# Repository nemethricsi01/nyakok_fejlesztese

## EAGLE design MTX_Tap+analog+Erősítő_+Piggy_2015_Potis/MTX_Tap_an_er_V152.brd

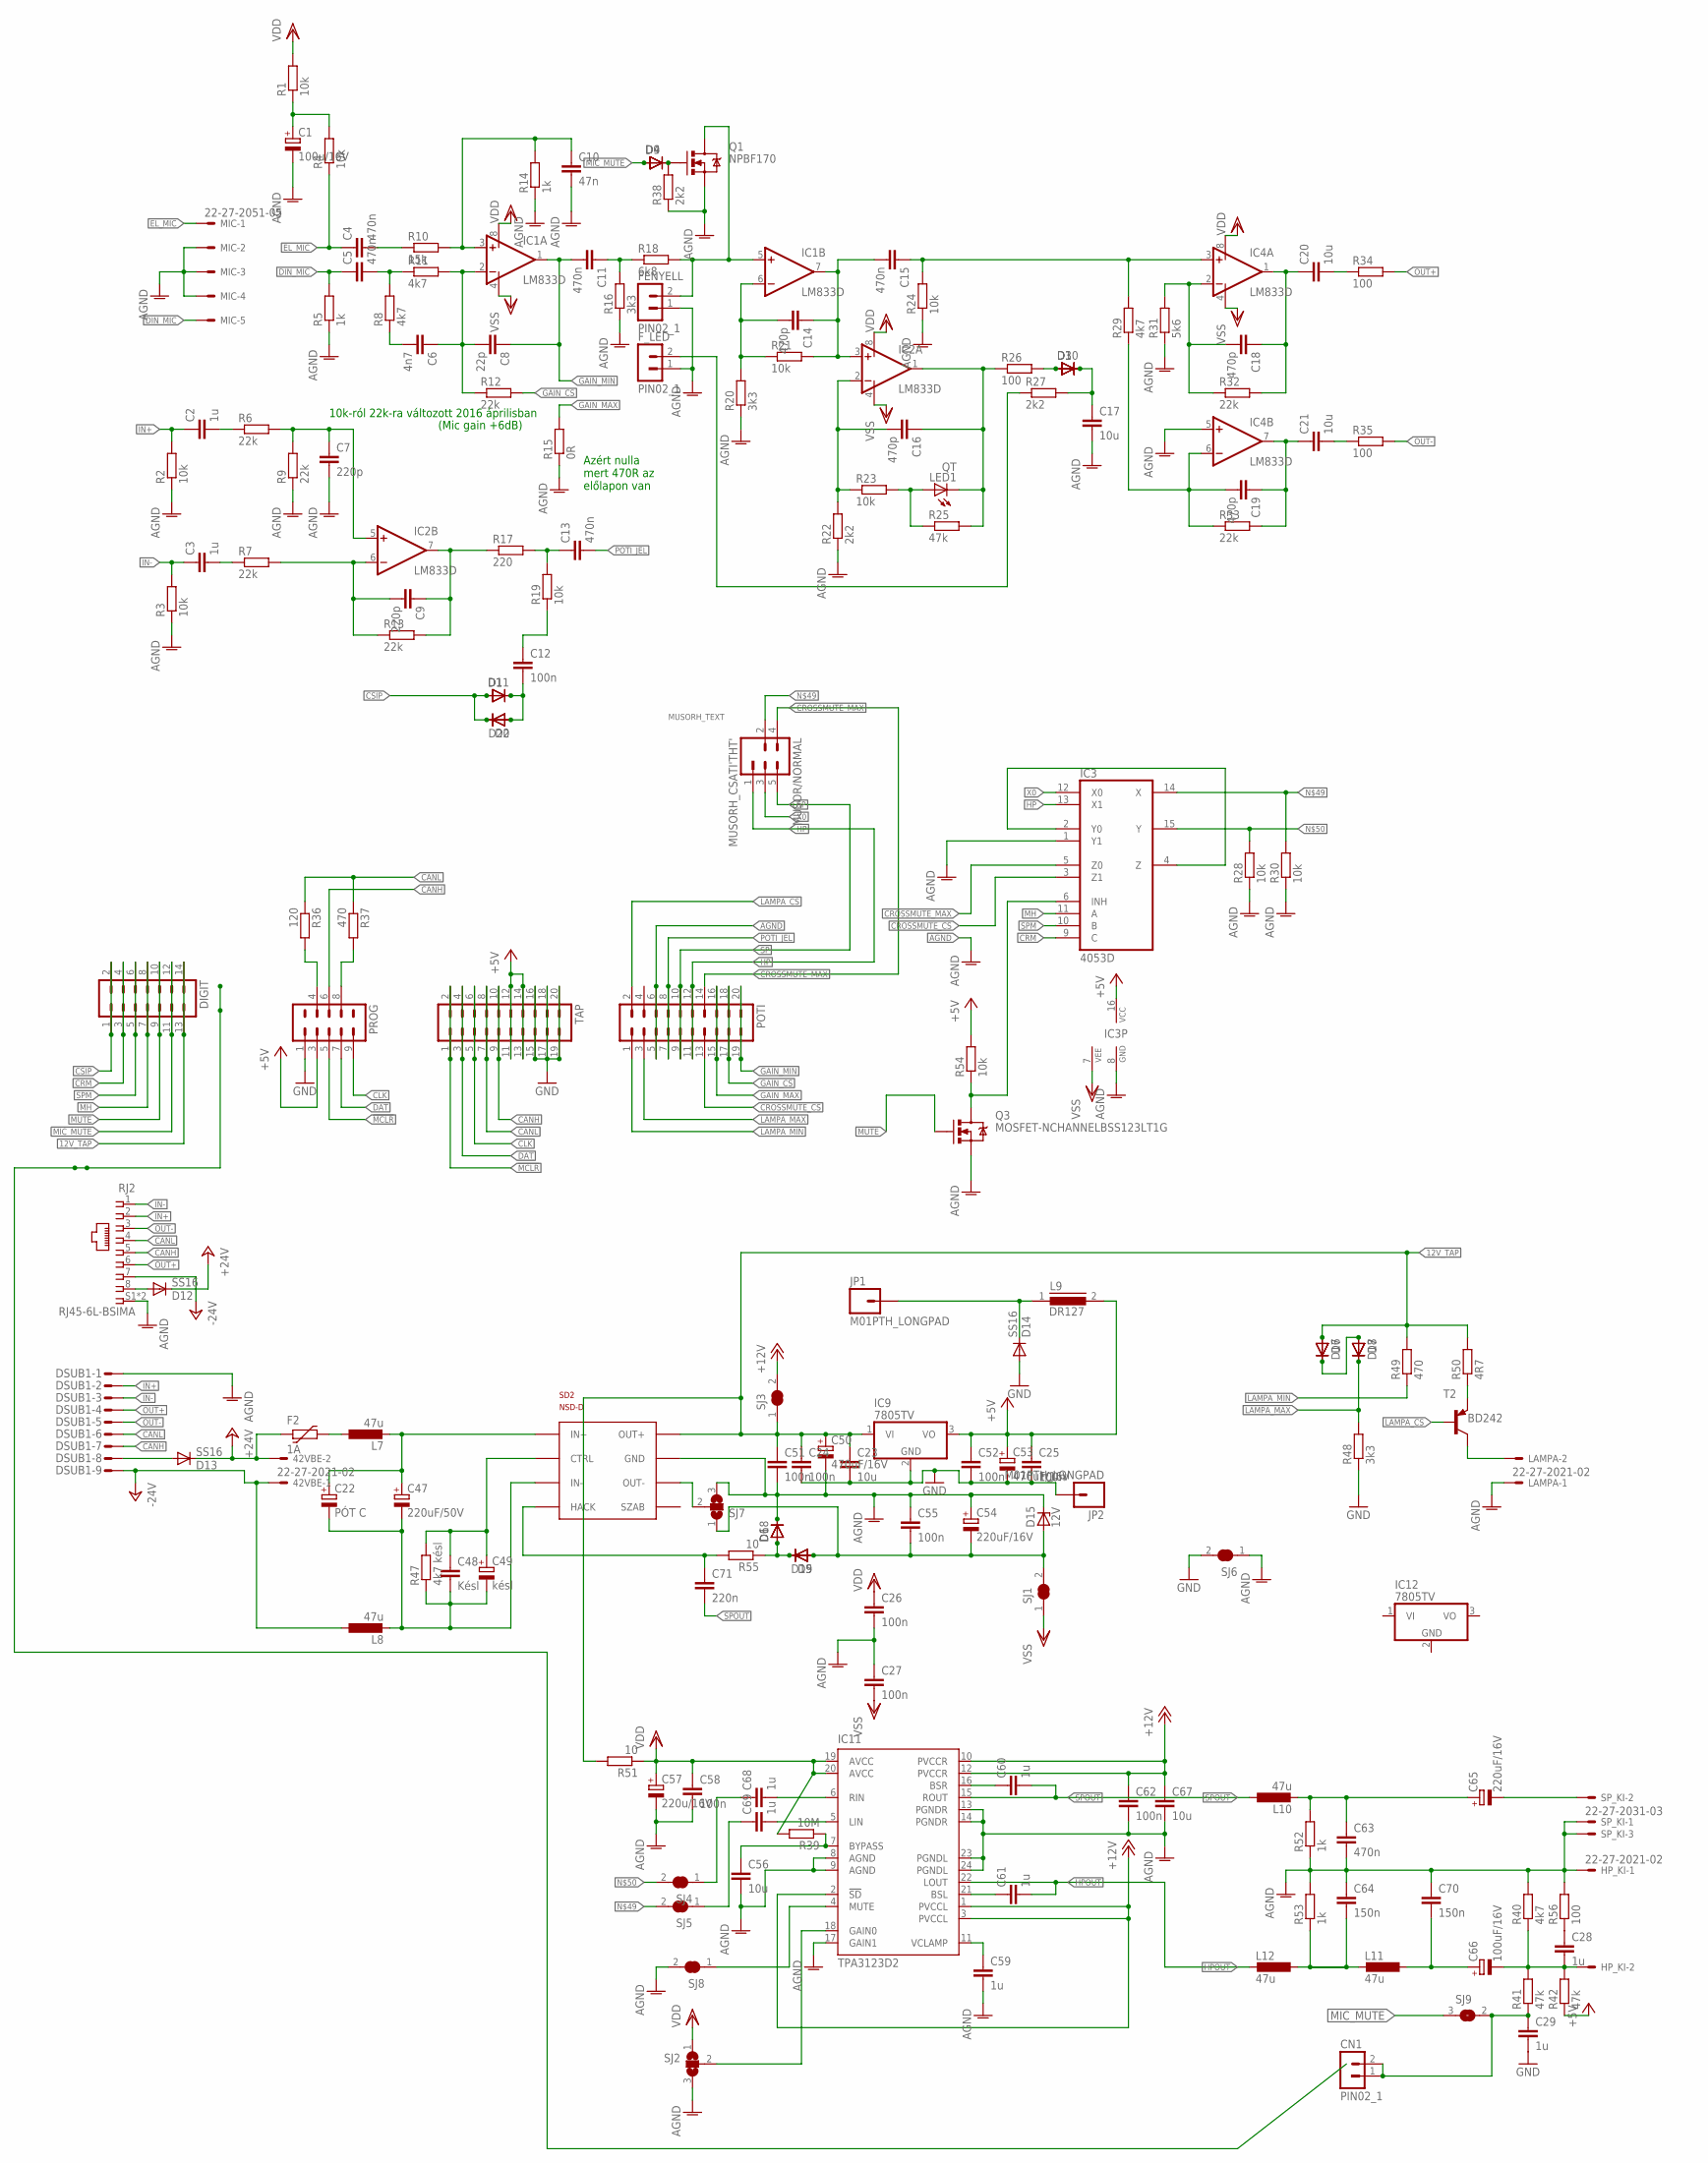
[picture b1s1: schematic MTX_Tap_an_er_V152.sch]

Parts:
42VBE: 22-27-2021-02; 6410-02
C1: 100u/16V; E2,5-5
C2, C3, C28, C29, C59, C60, C61, C68, C69: 1u; C0805
C4, C5, C11, C13, C15, C63: 470n; C0805
C6: 4n7; C0805
C7, C9: 220p; C0805
C8: 22p; C0805
C10: 47n; C0805
C12, C24, C25, C26, C27, C51, C52, C55, C58, C62: 100n; C0805
C14, C16, C18, C19: 470p; C0805
C17, C20, C21, C23, C56, C67: 10u; C0805
C22: PÓT C; E3,5-8
C47: 220uF/50V; E3,5-8
C48: Késl; C0805
C49: késl; E2,5-5
C50, C53: 470uF/16V; E3,5-8
C54, C65: 220uF/16V; E2,5-7
C57: 220u/16V; E2,5-7
C64, C70: 150n; C0805
C66: 100uF/16V; E2,5-6
C71: 220n; C0805
CN1: PIN02_1
D1, D2, D3, D4, D16, D17, D18, D19: 1N4148; DGLASSSMD
D5, D6, D7, D8, D9, D10, D11, D20: D0805
D12, D13, D14: SS16; DO-214AC
D15: 12V; SOD80C
DIGIT: MA07-2
DSUB1: M09-182S; 182-009-MALE
F2: 1A; PTC1812L
FENYELL: PIN02_1
F_LED: PIN02_1
HP_KI: 22-27-2021-02; 6410-02
IC1, IC2, IC4: LM833D; SO08
IC3: 4053D; SO16
IC9, IC12: 7805TV; TO220V
IC11: TPA3123D2; PWP-TSSOP24
JP1, JP2: M01PTH_LONGPAD; 1X01_LONGPAD
L7, L8, L10, L11, L12: 47u; PIS2816
L9: DR127
LAMPA: 22-27-2021-02; 6410-02
LED1: QT; LED3MM
MIC: 22-27-2051-05; 6410-05
MUSOR/NORMAL: MUSORH_CSATI'THT'; MUSORH_CSATI
POTI: MA10-2
PROG: CN_CANTAN
Q1: NPBF170; SOT23
Q3: MOSFET-NCHANNELBSS123LT1G; SOT23
R1, R2, R3, R4, R19, R21, R23, R24, R28, R30, R54: 10k; R0805
R5, R14, R52, R53: 1k; R0805
R6, R7, R9, R12, R13, R32, R33: 22k; R0805
R8, R11, R29, R40: 4k7; R0805
R10: 15k; R0805
R15: 0R; R0805
R16, R20, R48: 3k3; R0805
R17: 220; R0805
R18: 6k8; R0805
R22, R27, R38: 2k2; R0805
R25, R41, R42: 47k; R0805
R26, R34, R35, R56: 100; R0805
R31: 5k6; R0805
R36: 120; R0805
R37, R49: 470; R0805
R39: 10M; R0805
R47: 4k7 késl; R0805
R50: 4R7; R0805
R51: 10; R1210
R55: 10; R0805
RJ2: RJ45-6L-BSIMA; RJ45
SD2: NSD-D
SJ1, SJ3, SJ4, SJ5, SJ6, SJ8: SOLDERJUMPER_CLOSED; SOLDERJUMPER_CLOSEDWIRE
SJ2: SJ2WW12; SJ_2W_12
SJ7: SJ2WW23; SJ_2W_23
SJ9: SJ
SP_KI: 22-27-2031-03; 6410-03
T2: BD242; TO220V
TAP: MA10-2
U$1: MUSORH_TEXT

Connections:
1.: C9.1, IC2.7 (OUT), R13.2, R17.1
12V_TAP: C23.1, C24.1, C50.+, C51.1, D7.1 (A), D16.P$1 (A), DIGIT.13, DIGIT.14, IC9.1 (VI), R49.2, R50.2, R51.2, SD2.OUT+, SJ3.1
!MCLR: PROG.5, TAP.1, TAP.2
+5V: C25.1, C52.1, C53.+, IC3.16 (VCC), IC9.3 (VO), L9.2, PROG.3, R42.1, R54.2, TAP.11, TAP.12, TAP.13, TAP.14
+12V: C62.1, C67.1, IC11.1 (PVCCL), IC11.2 (!SD), IC11.3 (PVCCL), IC11.10 (PVCCR), IC11.12 (PVCCR), SJ3.2
+24V: 42VBE.2, D12.1 (C), D13.1 (C), F2.1
-24V: 42VBE.1, DSUB1.9, L8.1, RJ2.7
AGND: C1.-, C7.2, C10.2, C17.2, C26.2, C27.1, C50.-, C51.2, C54.+, C55.1, C56.2, C57.-, C58.2, C59.2, C62.2, C63.2, C64.1, C67.2, C70.1, D6.2 (C), D15.C, D18.P$2 (C), DSUB1.1, FENYELL.1, F_LED.1, HP_KI.1, IC3.1 (Y1), IC3.8 (GND), IC4.5 (+IN), IC11.8 (AGND), IC11.9 (AGND), IC11.13 (PGNDR), IC11.14 (PGNDR), IC11.17 (GAIN1), IC11.23 (PGNDL), IC11.24 (PGNDL), LAMPA.1, MIC.2, MIC.3, MIC.4, POTI.5, POTI.6, Q1.2 (S), Q3.2 (S), R2.1, R3.1, R5.1, R9.1, R14.1, R15.1, R16.1, R20.1, R22.1, R24.1, R28.1, R30.1, R31.1, R38.1, R40.2, R52.1, R53.2, R56.2, RJ2.S1 (S), RJ2.S2 (S), SD2.COMMON (GND), SJ2.3, SJ6.1, SJ7.3, SJ8.2, SP_KI.1, SP_KI.3
CANH: DSUB1.7, PROG.6, RJ2.5, TAP.9, TAP.10
CANL: DSUB1.6, R36.1, R37.1, RJ2.4, TAP.7, TAP.8
CLK: PROG.9, TAP.5, TAP.6
CRM: DIGIT.3, DIGIT.4, IC3.9 (C)
CROSSMUTE_CS: IC3.3 (Z1), POTI.13
CROSSMUTE_MAX: IC3.5 (Z0), MUSOR/NORMAL.4, POTI.14
CSIP: D1.P$1 (A), D2.P$2 (C), D11.1 (A), D20.2 (C), DIGIT.1, DIGIT.2
DAT: PROG.7, TAP.3, TAP.4
DIN_MIC: C5.1, MIC.5, R5.2
EL_MIC: C4.1, MIC.1, R4.1
GAIN_CS: POTI.17, POTI.18, R12.2
GAIN_MAX: POTI.15, POTI.16, R15.2
GAIN_MIN: C8.1, C11.2, IC1.1 (OUT), POTI.19, POTI.20
GND: C23.2, C24.2, C25.2, C29.2, C52.2, C53.-, D14.2 (A), IC9.2 (GND), JP2.1, PROG.1, R48.1, SJ6.2, TAP.15, TAP.16, TAP.17, TAP.18, TAP.19, TAP.20
HP: IC3.13 (X1), MUSOR/NORMAL.1, POTI.11, POTI.12
HPIN_X: C69.1, SJ5.1
HPOUT: C61.2, IC11.22 (LOUT), L12.2
IN+: C2.1, DSUB1.2, R2.2, RJ2.2
IN-: C3.1, DSUB1.3, R3.2, RJ2.1
LAMPA_CS: POTI.2, T2.1 (B)
LAMPA_MAX: D8.2 (C), D17.P$2 (C), POTI.3, R48.2
LAMPA_MIN: POTI.1, R49.1
MH: DIGIT.7, DIGIT.8, IC3.11 (A)
MIC_MUTE: D4.P$1 (A), D9.1 (A), DIGIT.11, DIGIT.12, SJ9.3 (1)
MUTE: DIGIT.9, DIGIT.10, Q3.1 (G)
unnamed: C1.+, R1.1, R4.2
unnamed: C4.2, R10.1
unnamed: C5.2, R8.2, R11.1
unnamed: C10.1, IC1.3 (+IN), R10.2, R14.2
unnamed: C6.1, C8.2, IC1.2 (-IN), R11.2, R12.1
unnamed: C54.-, C55.2, D5.1 (A), D15.A, D19.P$1 (A), SJ1.2, SJ7.1
unnamed: D12.2 (A), RJ2.8
unnamed: C6.2, R8.1
unnamed: FENYELL.2, IC1.5 (+IN), Q1.3 (D), R18.2
unnamed: C28.1, R56.1
unnamed: IC3.2 (Y0), IC3.4 (Z)
unnamed: C11.1, R16.2, R18.1
unnamed: C18.2, IC4.2 (-IN), R31.2, R32.1
unnamed: C18.1, C20.1, IC4.1 (OUT), R32.2
unnamed: C14.2, IC1.6 (-IN), R20.2, R21.1
unnamed: C14.1, C15.2, IC1.7 (OUT), IC2.3 (+IN), R21.2
unnamed: C16.2, IC2.2 (-IN), R22.2, R23.1
unnamed: C19.2, IC4.6 (-IN), R29.1, R33.1
unnamed: LED1.A, R23.2, R25.1
unnamed: C16.1, IC2.1 (OUT), LED1.K (C), R25.2, R26.1
unnamed: D3.P$1 (A), D10.1 (A), R26.2
unnamed: C17.1, D3.P$2 (C), D10.2 (C), R27.2
unnamed: F_LED.2, R27.1
unnamed: C15.1, IC4.3 (+IN), R24.2, R29.2
unnamed: C19.1, C21.1, IC4.7 (OUT), R33.2
unnamed: C21.2, R35.1
unnamed: C20.2, R34.1
unnamed: C2.2, R6.1
unnamed: D4.P$2 (C), D9.2 (C), Q1.1 (G), R38.2
unnamed: C7.1, IC2.5 (+IN), R6.2, R9.2
unnamed: C3.2, R7.1
unnamed: C65.-, SP_KI.2
unnamed: C12.2, D1.P$2 (C), D2.P$1 (A), D11.2 (C), D20.1 (A)
unnamed: C9.2, IC2.6 (-IN), R7.2, R13.1
unnamed: C29.1, CN1.1, CN1.2, R41.1, SJ9.2
unnamed: C13.1, R17.2, R19.2
unnamed: C12.1, R19.1
unnamed: SD2.OUT-, SJ7.2
unnamed: IC3.14 (X), MUSOR/NORMAL.2, R30.2, SJ5.2
unnamed: IC3.15 (Y), R28.2, SJ4.2
unnamed: PROG.8, R37.2
unnamed: C71.1, R55.2, SD2.HACK
unnamed: PROG.4, R36.2
unnamed: IC3.6 (INH), Q3.3 (D), R54.1
unnamed: D13.2 (A), DSUB1.8
unnamed: F2.2, L7.1
unnamed: C22.+, C47.+, L7.2, SD2.INPUT+ (IN+)
unnamed: C48.1, C49.+, R47.2, SD2.CONTROL (CTRL)
unnamed: C22.-, C47.-, C48.2, C49.-, L8.2, R47.1, SD2.INPUT- (IN-)
unnamed: D14.1 (C), JP1.1, L9.1
unnamed: R50.1, T2.3 (E)
unnamed: D7.2 (C), D8.1 (A), D16.P$2 (C), D17.P$1 (A)
unnamed: LAMPA.2, T2.2 (C)
unnamed: C56.1, IC11.7 (BYPASS), R39.1
unnamed: C59.1, IC11.11 (VCLAMP)
unnamed: C61.1, IC11.21 (BSL)
unnamed: C60.1, IC11.16 (BSR)
unnamed: C63.1, C65.+, L10.2, R52.2
unnamed: C64.2, L11.2, L12.1, R53.1
unnamed: C28.2, C66.-, HP_KI.2, R40.1, R41.2, R42.2
unnamed: C68.2, IC11.6 (RIN)
unnamed: C69.2, IC11.5 (LIN)
unnamed: IC11.18 (GAIN0), SJ2.2
unnamed: IC11.4 (MUTE), SJ8.1
unnamed: D5.2 (C), D6.1 (A), D18.P$1 (A), D19.P$2 (C), R55.1
unnamed: C66.+, C70.2, L11.1
OUT+: DSUB1.4, R34.2, RJ2.6
OUT-: DSUB1.5, R35.2, RJ2.3
POTI_JEL: C13.2, POTI.7, POTI.8
SP: MUSOR/NORMAL.5, POTI.9, POTI.10
SPIN_X: C68.1, SJ4.1
SPM: DIGIT.5, DIGIT.6, IC3.10 (B)
SPOUT: C60.2, C71.2, IC11.15 (ROUT), L10.1
VDD: C26.1, C57.+, C58.1, IC1.8 (V+), IC2.8 (V+), IC4.8 (V+), IC11.19 (AVCC), IC11.20 (AVCC), R1.2, R39.2, R51.1, SJ2.1
VSS: C27.2, IC1.4 (V-), IC2.4 (V-), IC3.7 (VEE), IC4.4 (V-), SJ1.1
X0: IC3.12 (X0), MUSOR/NORMAL.3

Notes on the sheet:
10k-ról 22k-ra változott 2016 áprilisban
(Mic gain +6dB)
Azért nulla mert 470R az előlapon van

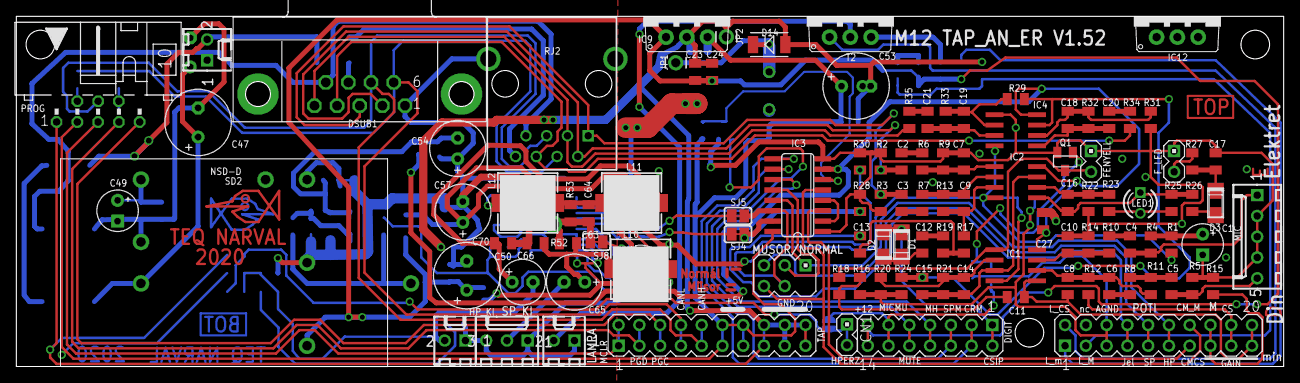
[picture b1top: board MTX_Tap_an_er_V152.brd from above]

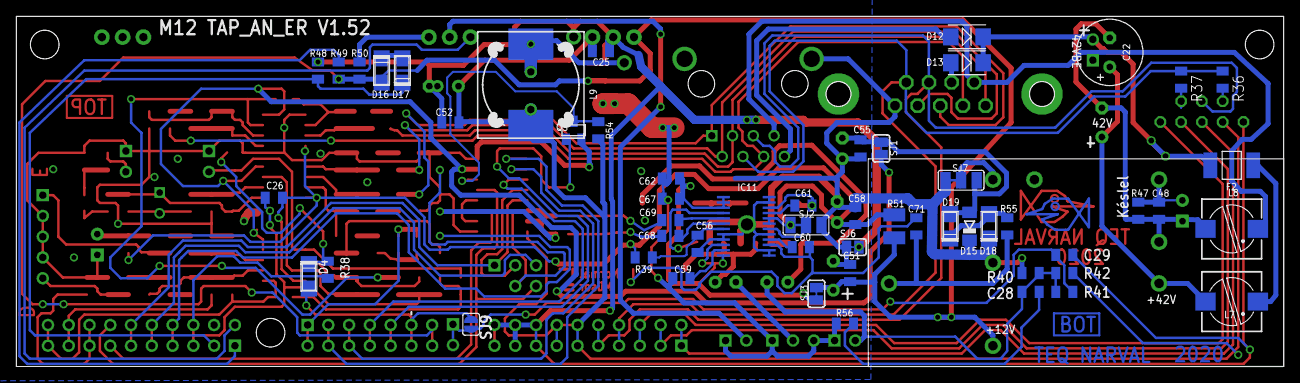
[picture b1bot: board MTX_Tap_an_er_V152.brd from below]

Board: 2 copper layers, 155.0 x 42.8 mm, 172 parts (59 on the bottom side), 109 nets.

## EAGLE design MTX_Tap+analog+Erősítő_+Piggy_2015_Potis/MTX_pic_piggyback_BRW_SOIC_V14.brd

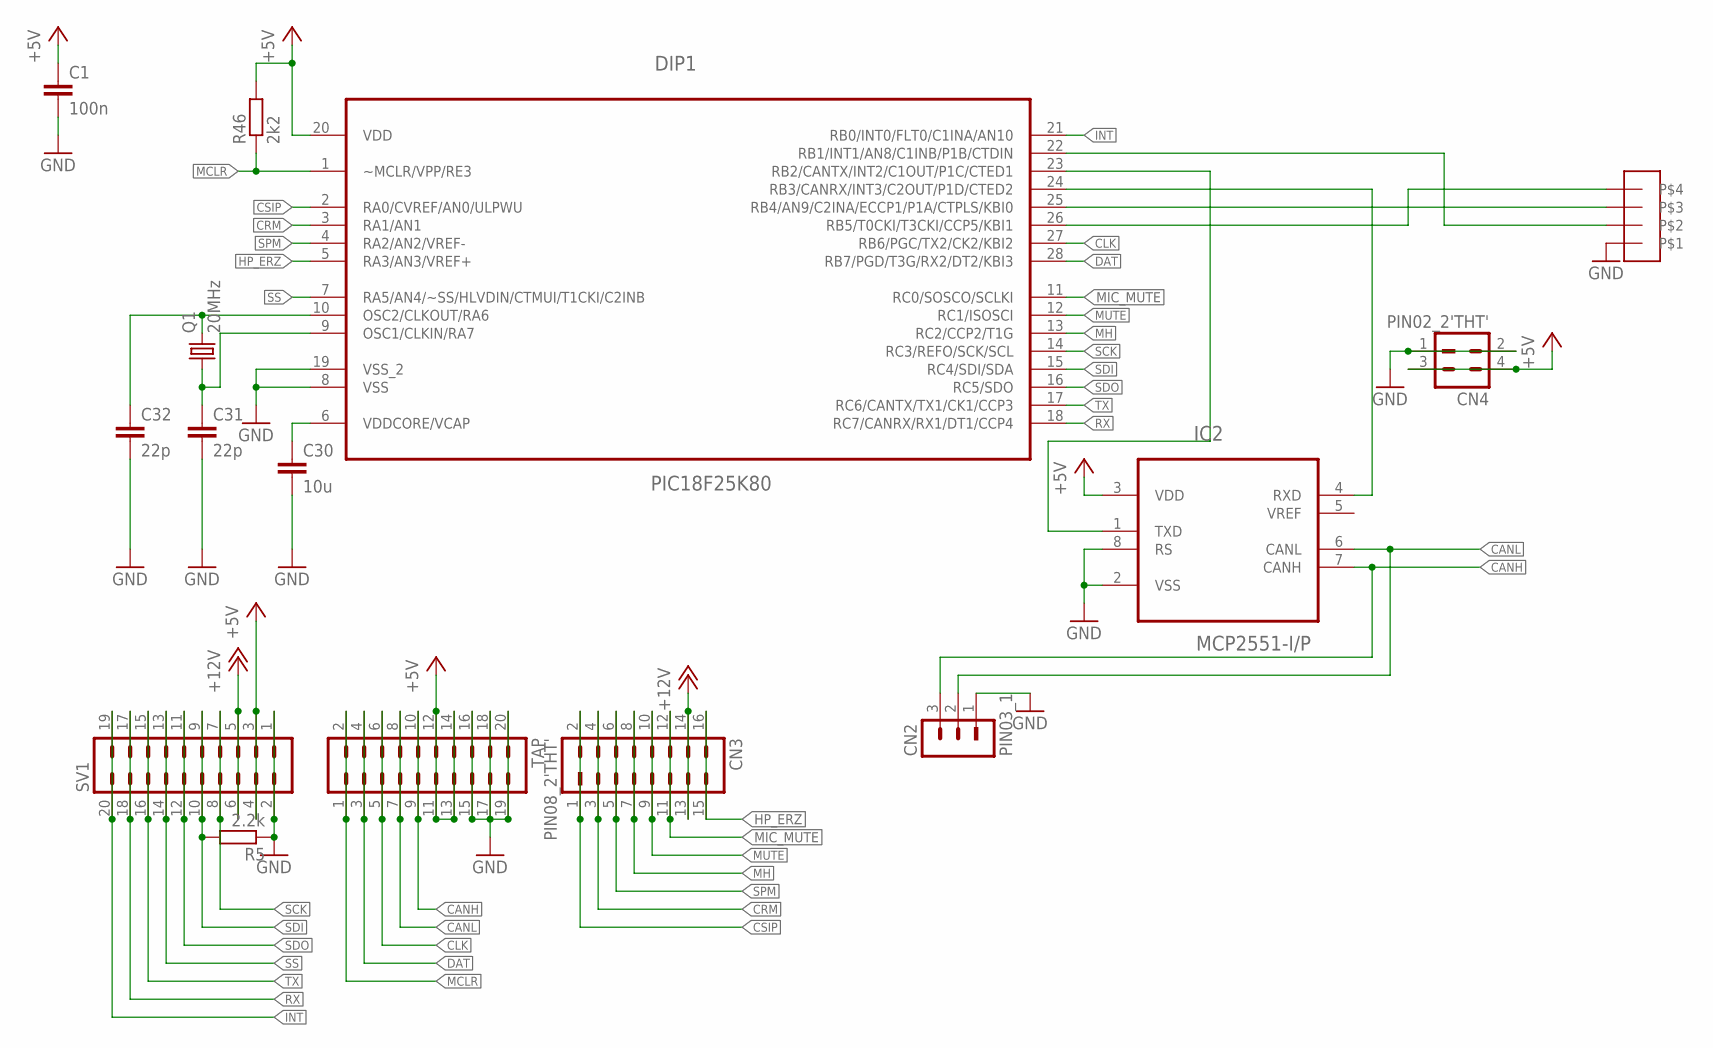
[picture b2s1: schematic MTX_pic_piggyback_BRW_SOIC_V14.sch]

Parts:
C1: 100n; C0805
C30: 10u; C0805
C31, C32: 22p; C0805
CN2: PIN03_1
CN3: PIN08_2'THT'; PIN08_2
CN4: PIN02_2'THT'; PIN02_2
DIP1: PIC18F25K80; SOIC127P1030X265-28N
IC2: MCP2551-I/P; DIP254P762X432-8
Q1: 20MHz; XTAL_QS
R5: 2.2k; R0805
R46: 2k2; R0805
SV1: MA10-2
TAP: MA10-2
U$1: FEHER_TUS_4

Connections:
+5V: C1.1, CN4.3, CN4.4, DIP1.20 (VDD), IC2.3 (VDD), R46.2, SV1.3, SV1.4, TAP.11, TAP.12, TAP.13, TAP.14
+12V: CN3.13, CN3.14, SV1.5, SV1.6
CANH: CN2.3, IC2.7 (CANH), TAP.9, TAP.10
CANL: CN2.2, IC2.6 (CANL), TAP.7, TAP.8
CLK: DIP1.27 (RB6/PGC/TX2/CK2/KBI2), TAP.5, TAP.6
CRM: CN3.3, CN3.4, DIP1.3 (RA1/AN1)
CSIP: CN3.1, CN3.2, DIP1.2 (RA0/CVREF/AN0/ULPWU)
DAT: DIP1.28 (RB7/PGD/T3G/RX2/DT2/KBI3), TAP.3, TAP.4
GND: C1.2, C30.2, C31.2, C32.2, CN2.1, CN4.1, CN4.2, DIP1.8 (VSS), DIP1.19 (VSS_2), IC2.2 (VSS), IC2.8 (RS), R5.1, SV1.1, SV1.2, TAP.15, TAP.16, TAP.17, TAP.18, TAP.19, TAP.20, U$1.P$1
HP_ERZ: CN3.15, CN3.16, DIP1.5 (RA3/AN3/VREF+)
INT: DIP1.21 (RB0/INT0/FLT0/C1INA/AN10), SV1.19, SV1.20
MCLR: DIP1.1 (~MCLR/VPP/RE3), R46.1, TAP.1, TAP.2
MH: CN3.7, CN3.8, DIP1.13 (RC2/CCP2/T1G)
MIC_MUTE: CN3.11, CN3.12, DIP1.11 (RC0/SOSCO/SCLKI)
MUTE: CN3.9, CN3.10, DIP1.12 (RC1/ISOSCI)
unnamed: DIP1.23 (RB2/CANTX/INT2/C1OUT/P1C/CTED1), IC2.1 (TXD)
unnamed: DIP1.26 (RB5/T0CKI/T3CKI/CCP5/KBI1), U$1.P$4
unnamed: DIP1.25 (RB4/AN9/C2INA/ECCP1/P1A/CTPLS/KBI0), U$1.P$3
unnamed: DIP1.22 (RB1/INT1/AN8/C1INB/P1B/CTDIN), U$1.P$2
unnamed: C30.1, DIP1.6 (VDDCORE/VCAP)
unnamed: C31.1, DIP1.9 (OSC1/CLKIN/RA7), Q1.1
unnamed: C32.1, DIP1.10 (OSC2/CLKOUT/RA6), Q1.2
unnamed: DIP1.24 (RB3/CANRX/INT3/C2OUT/P1D/CTED2), IC2.4 (RXD)
RX: DIP1.18 (RC7/CANRX/RX1/DT1/CCP4), SV1.17, SV1.18
SCK: DIP1.14 (RC3/REFO/SCK/SCL), SV1.7, SV1.8
SDI: DIP1.15 (RC4/SDI/SDA), R5.2, SV1.9, SV1.10
SDO: DIP1.16 (RC5/SDO), SV1.11, SV1.12
SPM: CN3.5, CN3.6, DIP1.4 (RA2/AN2/VREF-)
SS: DIP1.7 (RA5/AN4/~SS/HLVDIN/CTMUI/T1CKI/C2INB), SV1.13, SV1.14
TX: DIP1.17 (RC6/CANTX/TX1/CK1/CCP3), SV1.15, SV1.16

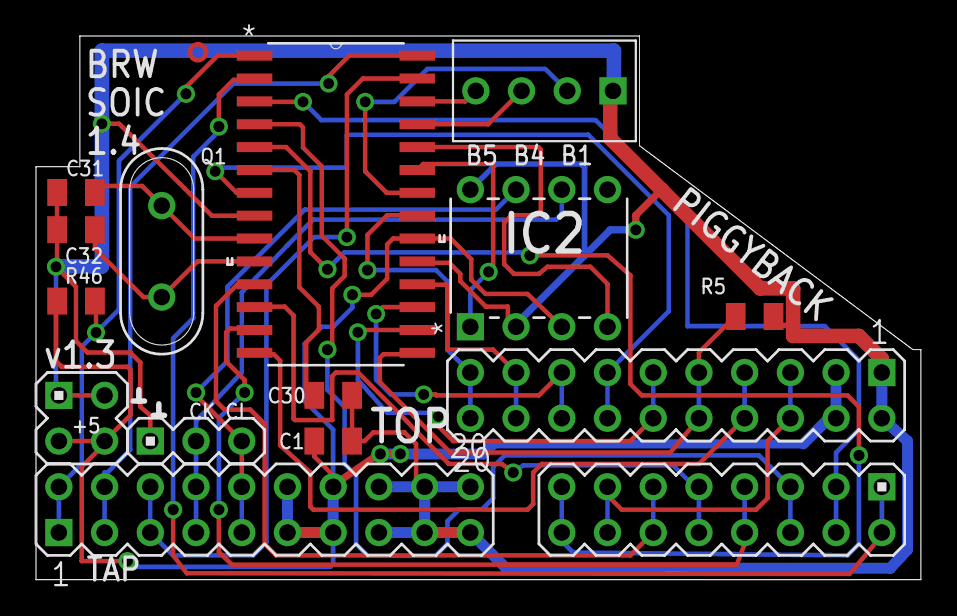
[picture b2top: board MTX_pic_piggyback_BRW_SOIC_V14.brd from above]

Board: 2 copper layers, 49.2 x 30.2 mm, 15 parts (0 on the bottom side), 30 nets.

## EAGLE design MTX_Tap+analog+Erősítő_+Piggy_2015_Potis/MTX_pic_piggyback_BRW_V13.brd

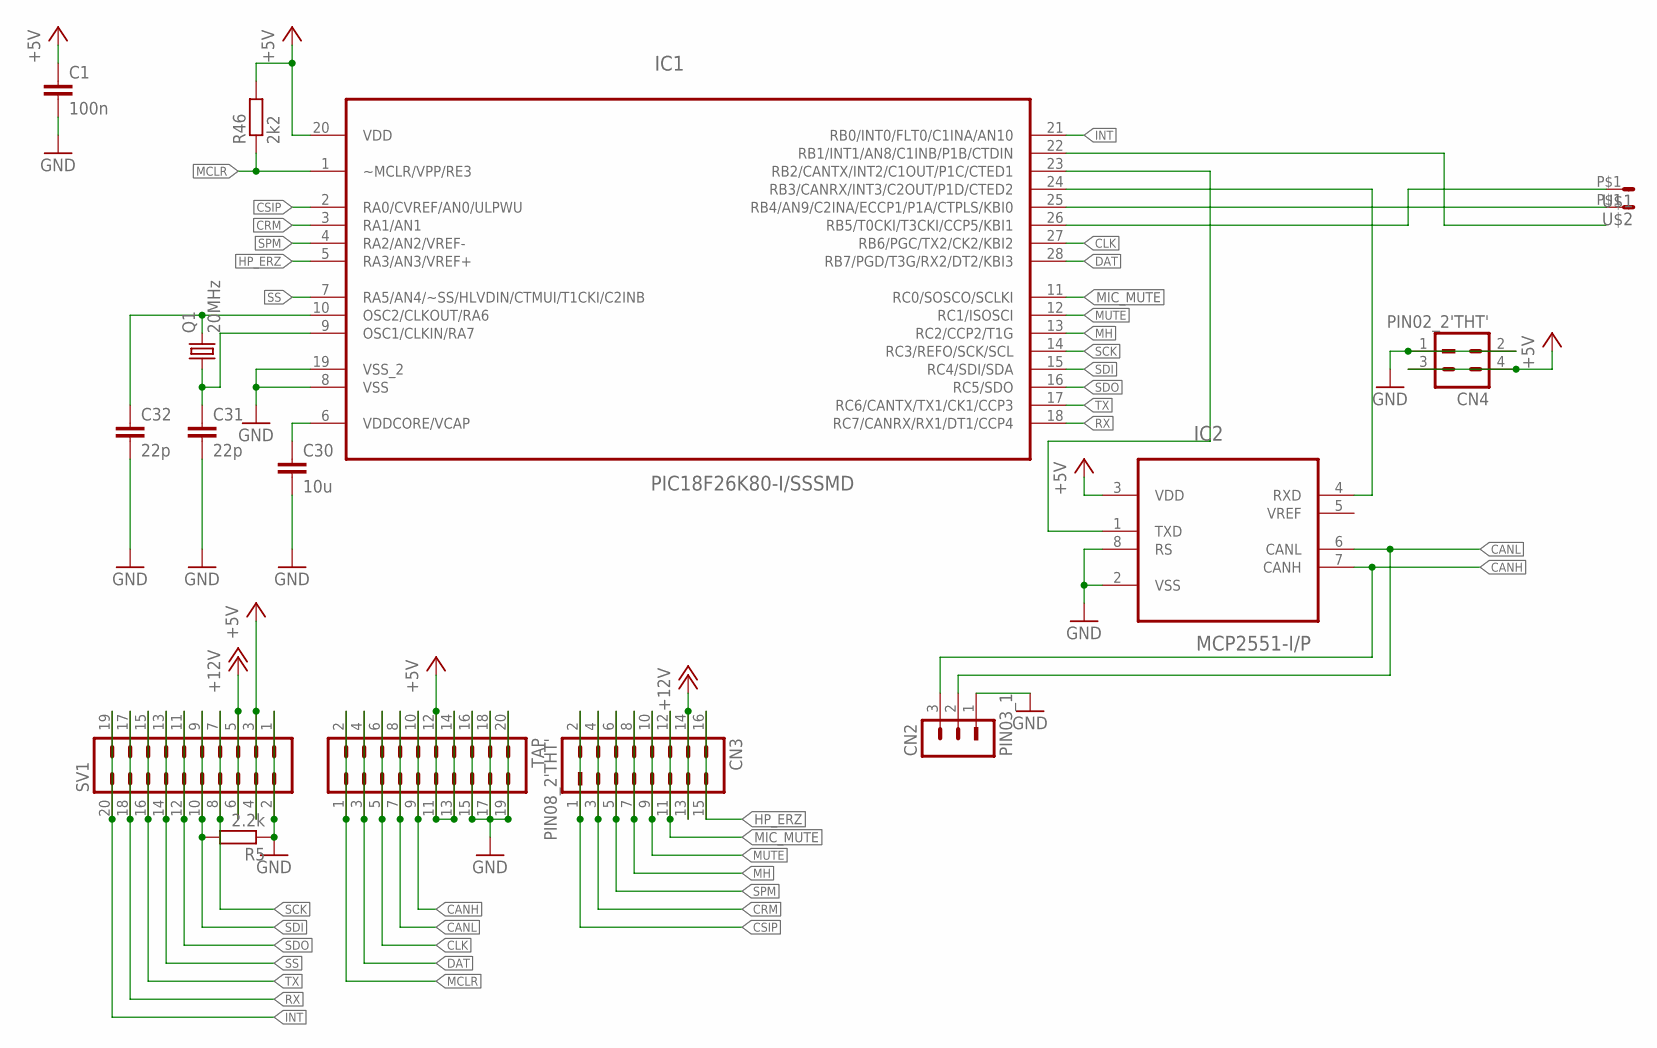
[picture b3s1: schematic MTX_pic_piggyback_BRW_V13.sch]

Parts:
C1: 100n; C0805
C30: 10u; C0805
C31, C32: 22p; C0805
CN2: PIN03_1
CN3: PIN08_2'THT'; PIN08_2
CN4: PIN02_2'THT'; PIN02_2
IC1: PIC18F26K80-I/SSSMD; SOP65P780X200-28N
IC2: MCP2551-I/P; DIP254P762X432-8
Q1: 20MHz; XTAL_QS
R5: 2.2k; R0805
R46: 2k2; R0805
SV1: MA10-2
TAP: MA10-2
U$1, U$2: PADSMD; PAD_SMD

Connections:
+5V: C1.1, CN4.3, CN4.4, IC1.20 (VDD), IC2.3 (VDD), R46.2, SV1.3, SV1.4, TAP.11, TAP.12, TAP.13, TAP.14
+12V: CN3.13, CN3.14, SV1.5, SV1.6
CANH: CN2.3, IC2.7 (CANH), TAP.9, TAP.10
CANL: CN2.2, IC2.6 (CANL), TAP.7, TAP.8
CLK: IC1.27 (RB6/PGC/TX2/CK2/KBI2), TAP.5, TAP.6
CRM: CN3.3, CN3.4, IC1.3 (RA1/AN1)
CSIP: CN3.1, CN3.2, IC1.2 (RA0/CVREF/AN0/ULPWU)
DAT: IC1.28 (RB7/PGD/T3G/RX2/DT2/KBI3), TAP.3, TAP.4
GND: C1.2, C30.2, C31.2, C32.2, CN2.1, CN4.1, CN4.2, IC1.8 (VSS), IC1.19 (VSS_2), IC2.2 (VSS), IC2.8 (RS), R5.1, SV1.1, SV1.2, TAP.15, TAP.16, TAP.17, TAP.18, TAP.19, TAP.20
HP_ERZ: CN3.15, CN3.16, IC1.5 (RA3/AN3/VREF+)
INT: IC1.21 (RB0/INT0/FLT0/C1INA/AN10), SV1.19, SV1.20
MCLR: IC1.1 (~MCLR/VPP/RE3), R46.1, TAP.1, TAP.2
MH: CN3.7, CN3.8, IC1.13 (RC2/CCP2/T1G)
MIC_MUTE: CN3.11, CN3.12, IC1.11 (RC0/SOSCO/SCLKI)
MUTE: CN3.9, CN3.10, IC1.12 (RC1/ISOSCI)
unnamed: IC1.23 (RB2/CANTX/INT2/C1OUT/P1C/CTED1), IC2.1 (TXD)
unnamed: IC1.26 (RB5/T0CKI/T3CKI/CCP5/KBI1), U$1.P$1
unnamed: IC1.25 (RB4/AN9/C2INA/ECCP1/P1A/CTPLS/KBI0), U$2.P$1
unnamed: C30.1, IC1.6 (VDDCORE/VCAP)
unnamed: C31.1, IC1.9 (OSC1/CLKIN/RA7), Q1.1
unnamed: C32.1, IC1.10 (OSC2/CLKOUT/RA6), Q1.2
unnamed: IC1.24 (RB3/CANRX/INT3/C2OUT/P1D/CTED2), IC2.4 (RXD)
RX: IC1.18 (RC7/CANRX/RX1/DT1/CCP4), SV1.17, SV1.18
SCK: IC1.14 (RC3/REFO/SCK/SCL), SV1.7, SV1.8
SDI: IC1.15 (RC4/SDI/SDA), R5.2, SV1.9, SV1.10
SDO: IC1.16 (RC5/SDO), SV1.11, SV1.12
SPM: CN3.5, CN3.6, IC1.4 (RA2/AN2/VREF-)
SS: IC1.7 (RA5/AN4/~SS/HLVDIN/CTMUI/T1CKI/C2INB), SV1.13, SV1.14
TX: IC1.17 (RC6/CANTX/TX1/CK1/CCP3), SV1.15, SV1.16

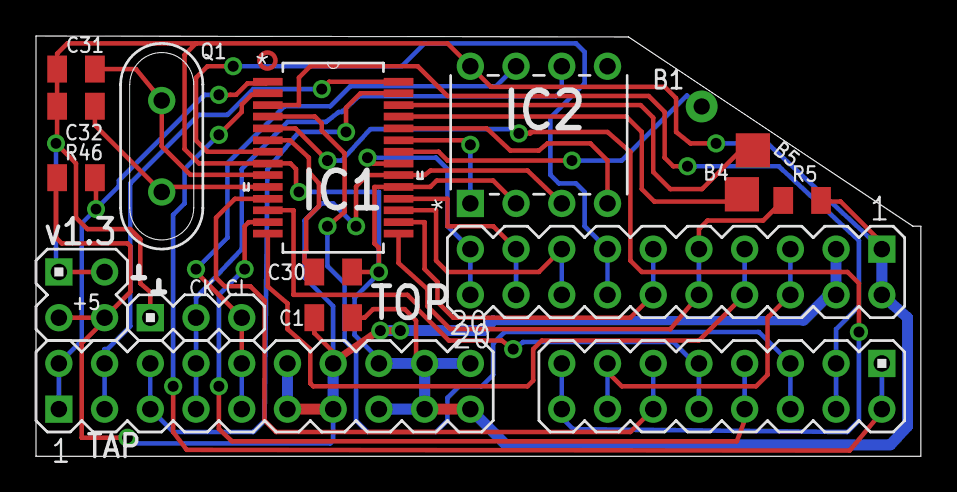
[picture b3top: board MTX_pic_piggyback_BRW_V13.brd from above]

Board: 2 copper layers, 49.2 x 23.3 mm, 16 parts (0 on the bottom side), 29 nets.

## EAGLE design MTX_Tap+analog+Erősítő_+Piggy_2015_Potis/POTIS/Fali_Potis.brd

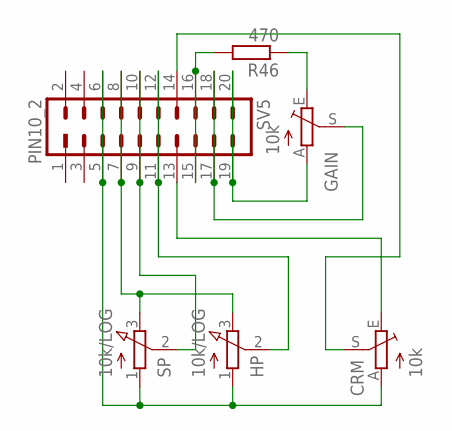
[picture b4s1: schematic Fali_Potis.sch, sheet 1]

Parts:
CRM: 10k; PT-10S
GAIN: 10k; PT-10S
HP: 10k/LOG; 3RP/1610N
R46: 470; R0805
SP: 10k/LOG; 3RP/1610N
SV5: PIN10_2

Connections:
unnamed: CRM.E, SV5.13
unnamed: CRM.A, HP.1 (A), SP.1 (A), SV5.5, SV5.6
unnamed: HP.3 (E), SP.3 (E), SV5.7, SV5.8
unnamed: SP.2 (S), SV5.9, SV5.10
unnamed: HP.2 (S), SV5.11, SV5.12
unnamed: CRM.S, SV5.14
unnamed: R46.2, SV5.15, SV5.16
unnamed: GAIN.S, SV5.17, SV5.18
unnamed: GAIN.A, SV5.19, SV5.20
unnamed: GAIN.E, R46.1

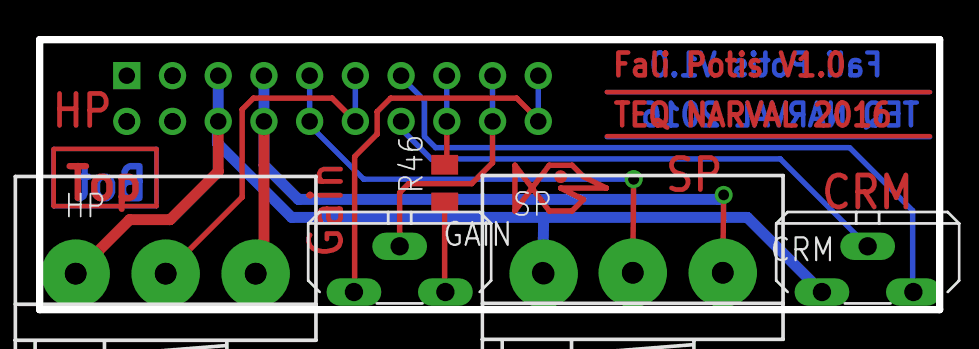
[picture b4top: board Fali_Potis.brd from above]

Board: 2 copper layers, 50.0 x 15.0 mm, 6 parts (1 on the bottom side), 10 nets.

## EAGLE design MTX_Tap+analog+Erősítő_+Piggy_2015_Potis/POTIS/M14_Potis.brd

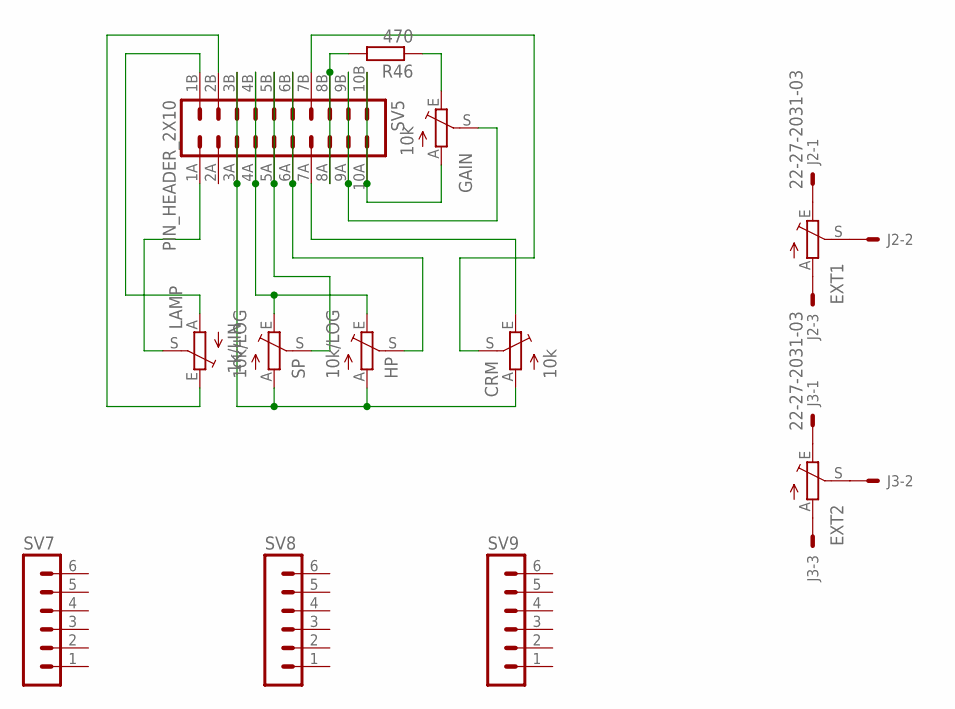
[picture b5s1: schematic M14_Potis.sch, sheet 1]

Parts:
CRM: 10k; PT-10
EXT1, EXT2: TRIM_EU-PT10; PT-10
GAIN: 10k; PT-10
HP: 10k/LOG; POT_NAR
J2, J3: 22-27-2031-03; 6410-03
LAMP: 1k/LIN; POT_NAR
R46: 470; R0805
SP: 10k/LOG; POT_NAR
SV5: PIN_HEADER_2X10; PIN_HEADER_2X10SMD
SV7, SV8, SV9: MA06-1

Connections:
unnamed: CRM.E, SV5.7A (13)
unnamed: CRM.A, HP.A, SP.A, SV5.3A (5), SV5.3B (6)
unnamed: HP.E, SP.E, SV5.4A (7), SV5.4B (8)
unnamed: SP.S, SV5.5A (9), SV5.5B (10)
unnamed: EXT1.S, J2.2
unnamed: EXT2.S, J3.2
unnamed: EXT1.E, J2.1
unnamed: EXT1.A, J2.3
unnamed: LAMP.S, SV5.1A (1)
unnamed: EXT2.A, J3.3
unnamed: EXT2.E, J3.1
unnamed: LAMP.E, SV5.2B (4)
unnamed: HP.S, SV5.6A (11), SV5.6B (12)
unnamed: LAMP.A, SV5.1B (2)
unnamed: CRM.S, SV5.7B (14)
unnamed: R46.2, SV5.8A (15), SV5.8B (16)
unnamed: GAIN.S, SV5.9A (17), SV5.9B (18)
unnamed: GAIN.A, SV5.10A (19), SV5.10B (20)
unnamed: GAIN.E, R46.1

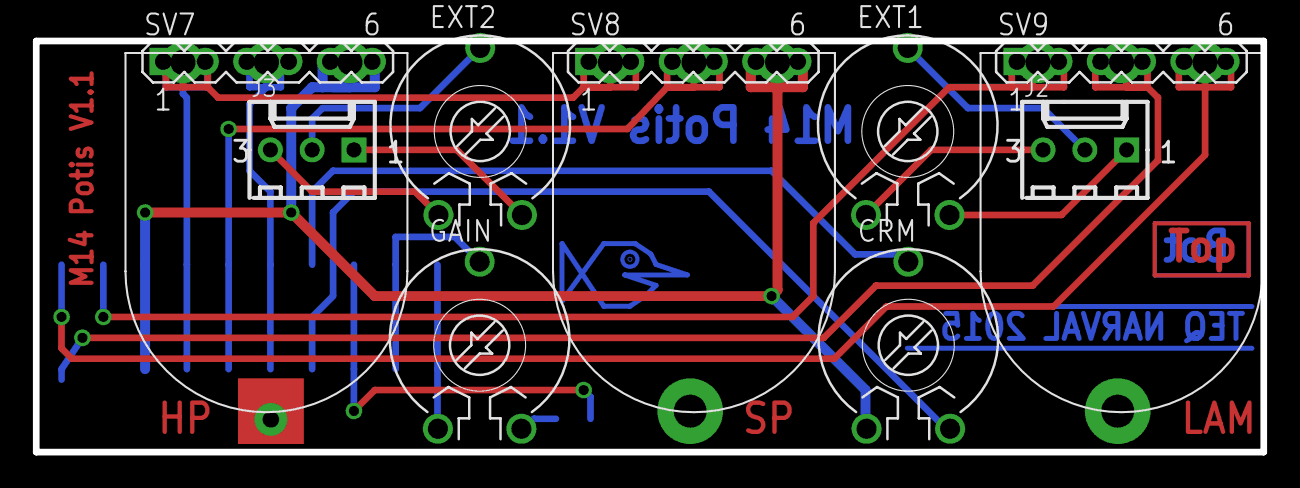
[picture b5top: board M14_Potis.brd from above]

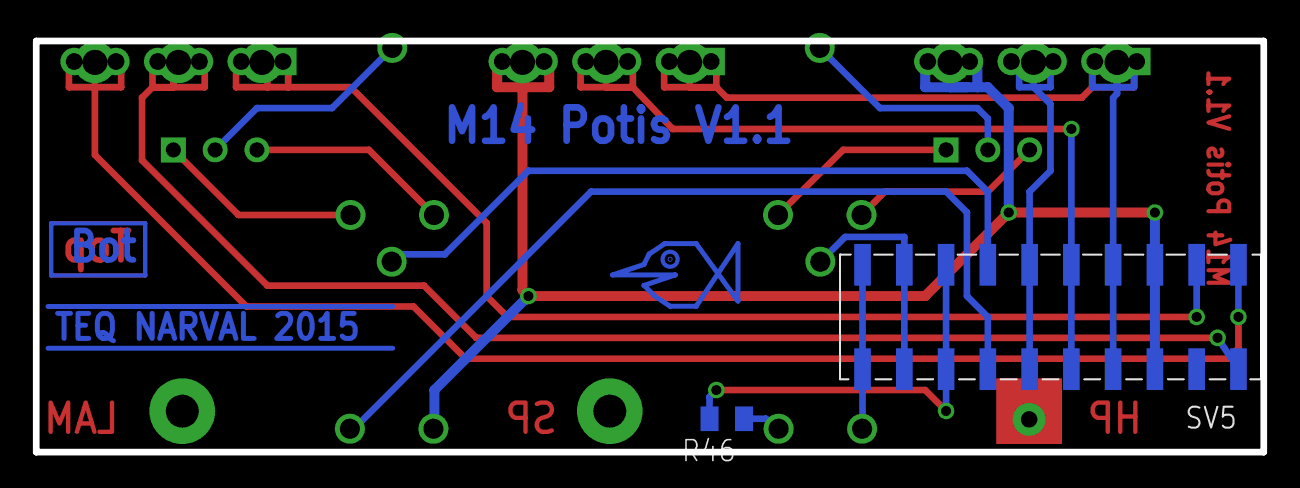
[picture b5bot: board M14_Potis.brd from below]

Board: 2 copper layers, 74.6 x 25.0 mm, 14 parts (2 on the bottom side), 19 nets.

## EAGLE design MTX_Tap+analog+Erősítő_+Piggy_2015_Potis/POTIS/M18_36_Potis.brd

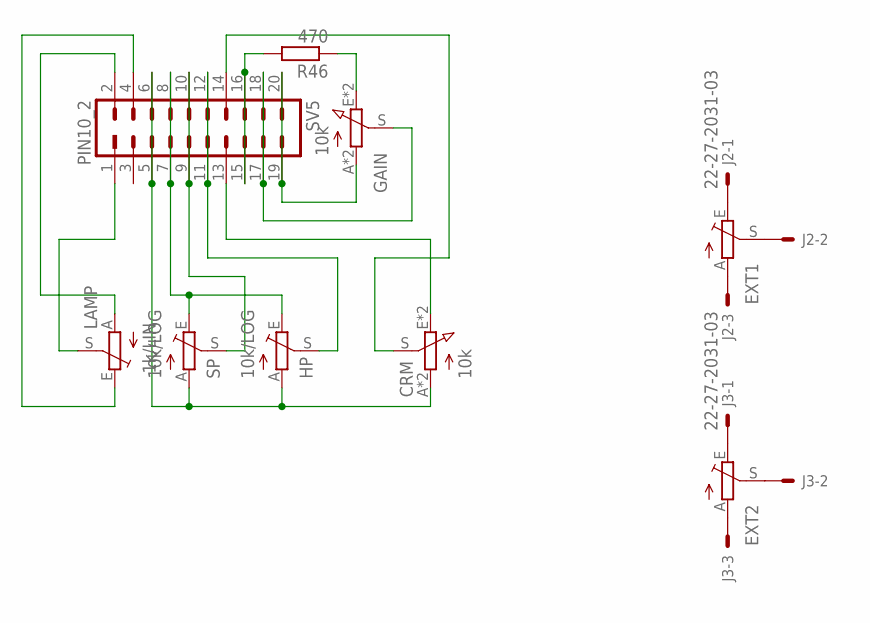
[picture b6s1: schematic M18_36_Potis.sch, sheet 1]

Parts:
CRM: 10k; P_PT-10+15_KIEMELT
EXT1, EXT2: TRIM_EU-PT10; PT-10
GAIN: 10k; P_PT-10+15_KIEMELT
HP: 10k/LOG; POT_NAR
J2, J3: 22-27-2031-03; 6410-03
LAMP: 1k/LIN; POT_NAR
R46: 470; R0805
SP: 10k/LOG; POT_NAR
SV5: PIN10_2

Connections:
unnamed: CRM.E, CRM.E1 (E), SV5.13
unnamed: CRM.A, CRM.A1 (A), HP.A, SP.A, SV5.5, SV5.6
unnamed: HP.E, SP.E, SV5.7, SV5.8
unnamed: SP.S, SV5.9, SV5.10
unnamed: EXT1.S, J2.2
unnamed: EXT2.S, J3.2
unnamed: EXT1.E, J2.1
unnamed: EXT1.A, J2.3
unnamed: LAMP.S, SV5.1
unnamed: EXT2.A, J3.3
unnamed: EXT2.E, J3.1
unnamed: LAMP.E, SV5.4
unnamed: HP.S, SV5.11, SV5.12
unnamed: LAMP.A, SV5.2
unnamed: CRM.S, SV5.14
unnamed: R46.2, SV5.15, SV5.16
unnamed: GAIN.S, SV5.17, SV5.18
unnamed: GAIN.A, GAIN.A1 (A), SV5.19, SV5.20
unnamed: GAIN.E, GAIN.E1 (E), R46.1

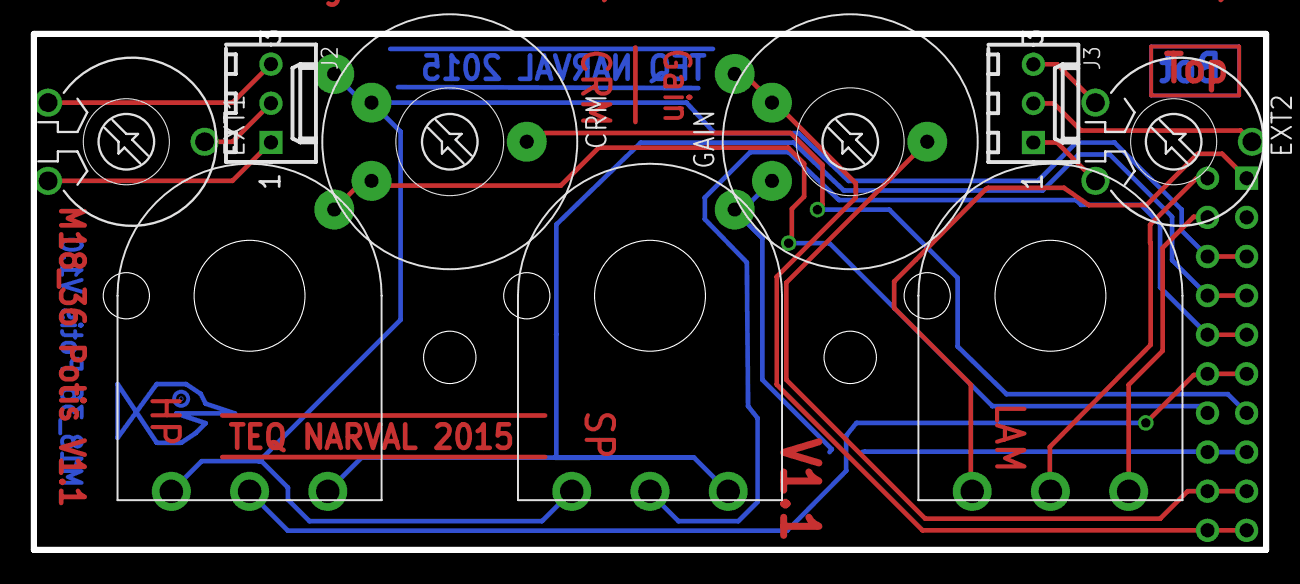
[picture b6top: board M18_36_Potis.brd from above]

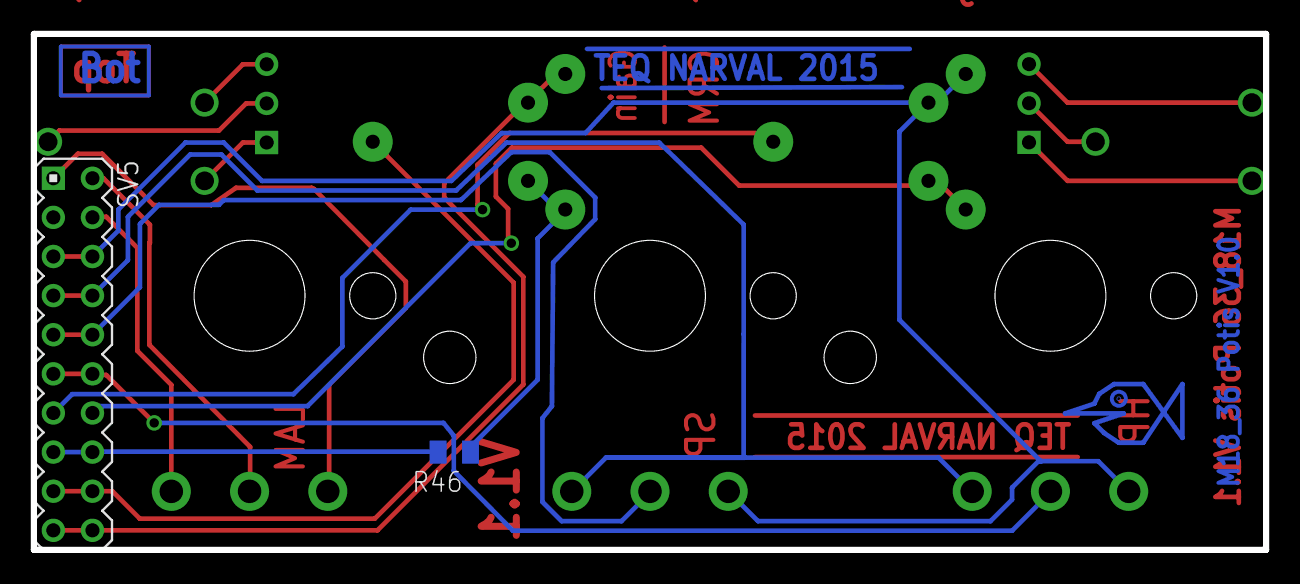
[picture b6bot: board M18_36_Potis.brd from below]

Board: 2 copper layers, 80.0 x 33.5 mm, 11 parts (2 on the bottom side), 19 nets.

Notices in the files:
parts and their libraries:
SparkFun-DiscreteSemi: Licensing: Creative Commons ShareAlike 4.0 International - https://creativecommons.org/licenses/by-sa/4.0
microbuilder: This work is placed in the public domain, and may be freely used for commercial and non-commercial work with the following conditions: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
